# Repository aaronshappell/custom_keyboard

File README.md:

# custom_keyboard
Various files and resources for my handmade custom mechanical keyboard.

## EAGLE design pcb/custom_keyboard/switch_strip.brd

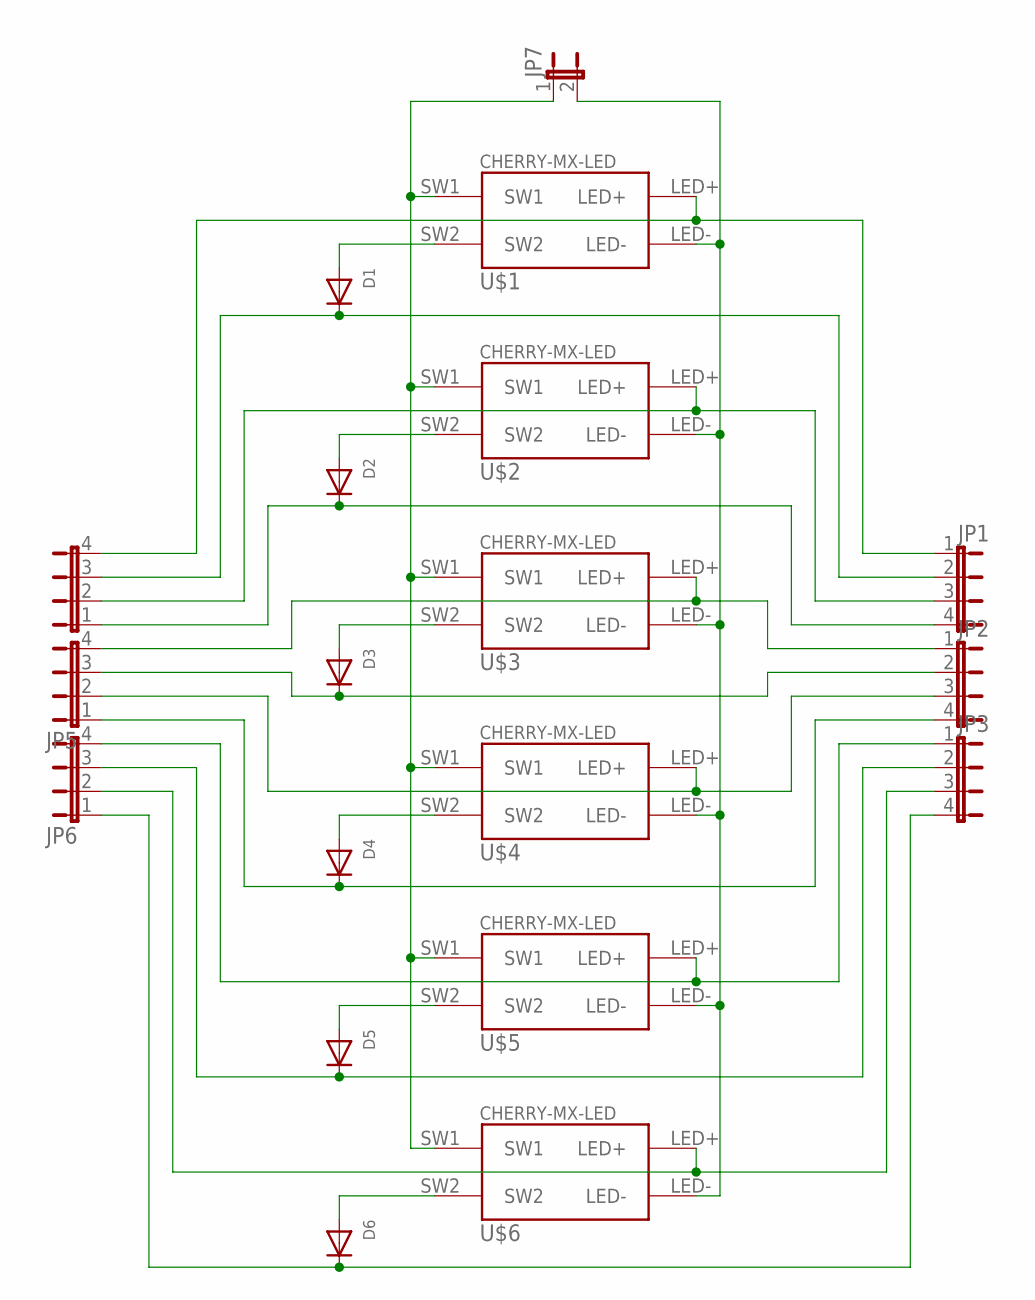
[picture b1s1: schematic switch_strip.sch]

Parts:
D1, D2, D3, D4, D5, D6: DIODEDO-1N4148; DO-1N4148
JP1, JP2, JP3, JP4, JP5, JP6: JP4E; JP4
JP7: JP1E; JP1
U$1, U$2, U$3, U$4, U$5, U$6: CHERRY-MX-LED

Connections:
unnamed: JP7.1, U$1.SW1, U$2.SW1, U$3.SW1, U$4.SW1, U$5.SW1, U$6.SW1
unnamed: D6.A, U$6.SW2
unnamed: D5.A, U$5.SW2
unnamed: D4.A, U$4.SW2
unnamed: D3.A, U$3.SW2
unnamed: D2.A, U$2.SW2
unnamed: D1.A, U$1.SW2
unnamed: JP7.2, U$1.LED-, U$2.LED-, U$3.LED-, U$4.LED-, U$5.LED-, U$6.LED-
unnamed: JP1.1, JP4.4, U$1.LED+
unnamed: D1.C, JP1.2, JP4.3
unnamed: JP1.3, JP4.2, U$2.LED+
unnamed: D2.C, JP1.4, JP4.1
unnamed: JP2.1, JP5.4, U$3.LED+
unnamed: D3.C, JP2.2, JP5.3
unnamed: JP2.3, JP5.2, U$4.LED+
unnamed: D4.C, JP2.4, JP5.1
unnamed: JP3.1, JP6.4, U$5.LED+
unnamed: D5.C, JP3.2, JP6.3
unnamed: JP3.3, JP6.2, U$6.LED+
unnamed: D6.C, JP3.4, JP6.1

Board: 2 copper layers, 19 parts (0 on the bottom side), 20 nets, no tracks yet.

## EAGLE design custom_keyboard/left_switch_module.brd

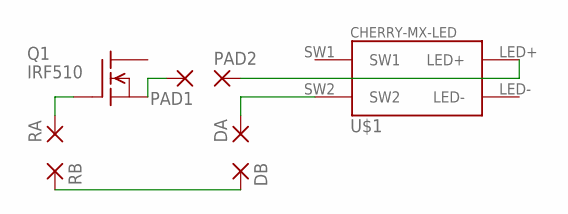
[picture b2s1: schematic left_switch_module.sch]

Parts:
DA: 2,15/1,0
DB: 2,15/1,0
PAD1, PAD2: 1,6/0,9
Q1: IRF510; TO220
RA: 2,15/1,0
RB: 2,15/1,0
U$1: CHERRY-MX-LED

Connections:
unnamed: Q1.1 (G), RA.1
unnamed: DB.1, RB.1
unnamed: DA.1, U$1.SW2
unnamed: PAD1.1, Q1.3 (S)
unnamed: PAD2.1, U$1.LED+

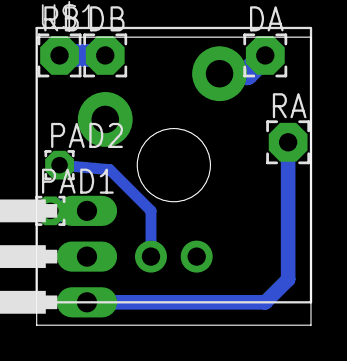
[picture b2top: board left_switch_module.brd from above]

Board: 2 copper layers, 15.2 x 16.0 mm, 8 parts (0 on the bottom side), 5 nets.

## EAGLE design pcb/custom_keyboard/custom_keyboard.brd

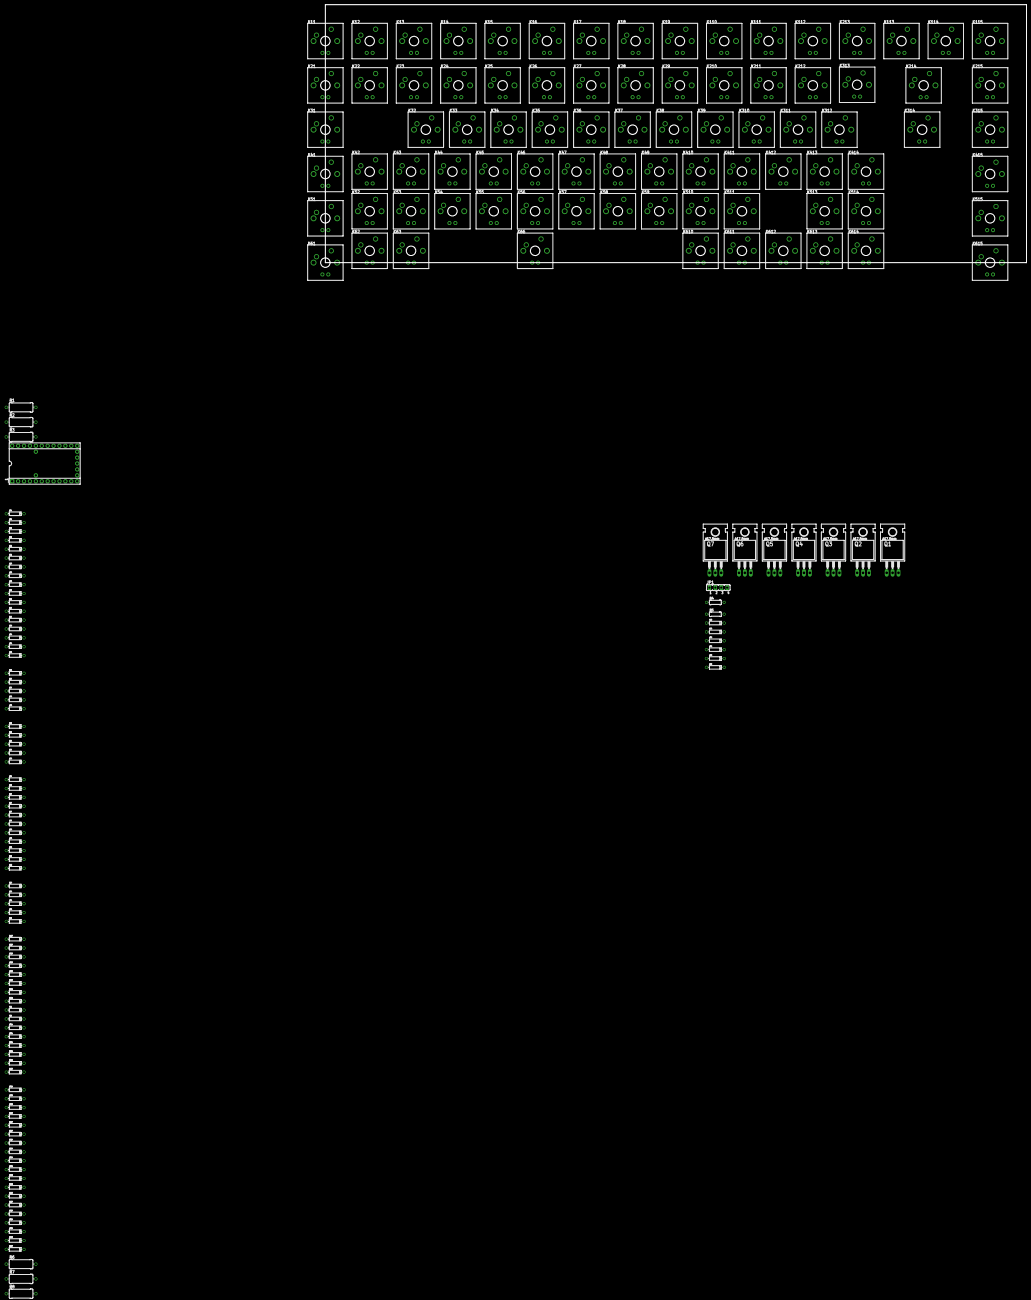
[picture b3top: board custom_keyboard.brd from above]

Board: 2 copper layers, 301.4 x 110.9 mm, 185 parts (0 on the bottom side), 120 nets, no tracks yet.

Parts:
311, 411: DO-1N4148
D11, D12, D13, D14, D15, D16, D17, D18, D19, D21, D22, D23, D24, D25, D26, D27, D28, D29, D31, D32, D33, D34, D35, D36, D37, D38, D39, D41, D42, D43, D44, D45, D46, D47, D48, D49, D51, D52, D53, D54, D55, D56, D57, D58, D59, D61, D62, D63, D66, D110, D111, D112, D113, D114, D115, D210, D211, D212, D213, D214, D215, D310, D312, D313, D314, D315, D410, D412, D413, D414, D415, D510, D511, D513, D514, D515, D610, D611, D612, D613, D614, D615: DO-1N4148
JP1: JP4
K11, K12, K13, K14, K15, K16, K17, K18, K19, K21, K22, K23, K24, K25, K26, K27, K28, K29, K31, K32, K33, K34, K35, K36, K37, K38, K39, K41, K42, K43, K44, K45, K46, K47, K48, K49, K51, K52, K53, K54, K55, K56, K57, K58, K59, K61, K62, K63, K66, K110, K111, K112, K113, K114, K115, K210, K211, K212, K213, K214, K215, K310, K311, K312, K313, K314, K315, K410, K411, K412, K413, K414, K415, K510, K511, K513, K514, K515, K610, K611, K612, K613, K614, K615: CHERRY-MX-LED
Q1, Q2, Q3, Q4, Q5, Q6, Q7: IRF510; TO220
R1, R2, R6, R7, R8: 6.8Ω; 0411/12
R3: 10Ω; 0411/12
R4, R5: 4.7kΩ; 0204/7
_1: TEENSY

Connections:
unnamed: D11.A, K11.SW2
unnamed: D12.A, K12.SW2
unnamed: D22.A, K22.SW2
unnamed: D21.A, K21.SW2
unnamed: D31.A, K31.SW2
unnamed: D41.A, K41.SW2
unnamed: D51.A, K51.SW2
unnamed: D61.A, K61.SW2
unnamed: D32.A, K32.SW2
unnamed: D42.A, K42.SW2
unnamed: D52.A, K52.SW2
unnamed: D62.A, K62.SW2
unnamed: D13.A, K13.SW2
unnamed: D23.A, K23.SW2
unnamed: D33.A, K33.SW2
unnamed: D43.A, K43.SW2
unnamed: D53.A, K53.SW2
unnamed: D63.A, K63.SW2
unnamed: D14.A, K14.SW2
unnamed: D24.A, K24.SW2
unnamed: D34.A, K34.SW2
unnamed: D44.A, K44.SW2
unnamed: D54.A, K54.SW2
unnamed: D11.C, D12.C, D13.C, D14.C, D15.C, D16.C, D17.C, D18.C, D19.C, D110.C, D111.C, D112.C, D113.C, D114.C, D115.C, Q1.1
unnamed: D15.A, K15.SW2
unnamed: D25.A, K25.SW2
unnamed: D35.A, K35.SW2
unnamed: D45.A, K45.SW2
unnamed: D55.A, K55.SW2
unnamed: D21.C, D22.C, D23.C, D24.C, D25.C, D26.C, D27.C, D28.C, D29.C, D210.C, D211.C, D212.C, D213.C, D214.C, D215.C, Q2.1
unnamed: D16.A, K16.SW2
unnamed: D26.A, K26.SW2
unnamed: D36.A, K36.SW2
unnamed: D46.A, K46.SW2
unnamed: D56.A, K56.SW2
unnamed: 311.C, D31.C, D32.C, D33.C, D34.C, D35.C, D36.C, D37.C, D38.C, D39.C, D310.C, D312.C, D313.C, D314.C, D315.C, Q3.1
unnamed: D17.A, K17.SW2
unnamed: D27.A, K27.SW2
unnamed: D37.A, K37.SW2
unnamed: D47.A, K47.SW2
unnamed: D57.A, K57.SW2
unnamed: D66.A, K66.SW2
unnamed: D18.A, K18.SW2
unnamed: D28.A, K28.SW2
unnamed: D38.A, K38.SW2
unnamed: D48.A, K48.SW2
unnamed: D58.A, K58.SW2
unnamed: 411.C, D41.C, D42.C, D43.C, D44.C, D45.C, D46.C, D47.C, D48.C, D49.C, D410.C, D412.C, D413.C, D414.C, D415.C, Q4.1
unnamed: D19.A, K19.SW2
unnamed: D29.A, K29.SW2
unnamed: D39.A, K39.SW2
unnamed: D49.A, K49.SW2
unnamed: D59.A, K59.SW2
unnamed: D51.C, D52.C, D53.C, D54.C, D55.C, D56.C, D57.C, D58.C, D59.C, D510.C, D511.C, D513.C, D514.C, D515.C, Q5.1
unnamed: D110.A, K110.SW2
unnamed: D210.A, K210.SW2
unnamed: D310.A, K310.SW2
unnamed: D410.A, K410.SW2
unnamed: D510.A, K510.SW2
unnamed: D610.A, K610.SW2
unnamed: D111.A, K111.SW2
unnamed: D211.A, K211.SW2
unnamed: 311.A, K311.SW2
unnamed: 411.A, K411.SW2
unnamed: D511.A, K511.SW2
unnamed: D611.A, K611.SW2
unnamed: D112.A, K112.SW2
unnamed: D212.A, K212.SW2
unnamed: D312.A, K312.SW2
unnamed: D412.A, K412.SW2
unnamed: D61.C, D62.C, D63.C, D66.C, D610.C, D611.C, D612.C, D613.C, D614.C, D615.C, Q6.1
unnamed: D612.A, K612.SW2
unnamed: D113.A, K113.SW2
unnamed: D213.A, K213.SW2
unnamed: D313.A, K313.SW2
unnamed: D413.A, K413.SW2
unnamed: D513.A, K513.SW2
unnamed: D613.A, K613.SW2
unnamed: D114.A, K114.SW2
unnamed: D214.A, K214.SW2
unnamed: D314.A, K314.SW2
unnamed: D414.A, K414.SW2
unnamed: D514.A, K514.SW2
unnamed: D614.A, K614.SW2
unnamed: D115.A, K115.SW2
unnamed: D215.A, K215.SW2
unnamed: D315.A, K315.SW2
unnamed: D415.A, K415.SW2
unnamed: D515.A, K515.SW2
unnamed: D615.A, K615.SW2
unnamed: K11.SW1, K21.SW1, K31.SW1, K41.SW1, K51.SW1, K61.SW1
unnamed: K12.SW1, K22.SW1, K32.SW1, K42.SW1, K52.SW1, K62.SW1
unnamed: K13.SW1, K23.SW1, K33.SW1, K43.SW1, K53.SW1, K63.SW1
unnamed: K14.SW1, K24.SW1, K34.SW1, K44.SW1, K54.SW1
unnamed: K115.SW1, K215.SW1, K315.SW1, K415.SW1, K515.SW1, K615.SW1
unnamed: K114.SW1, K214.SW1, K314.SW1, K414.SW1, K514.SW1, K614.SW1
unnamed: K113.SW1, K213.SW1, K313.SW1, K413.SW1, K513.SW1, K613.SW1
unnamed: K112.SW1, K212.SW1, K312.SW1, K412.SW1, K612.SW1
unnamed: K111.SW1, K211.SW1, K311.SW1, K411.SW1, K511.SW1, K611.SW1
unnamed: K110.SW1, K210.SW1, K310.SW1, K410.SW1, K510.SW1, K610.SW1
unnamed: K19.SW1, K29.SW1, K39.SW1, K49.SW1, K59.SW1
unnamed: K18.SW1, K28.SW1, K38.SW1, K48.SW1, K58.SW1
unnamed: K17.SW1, K27.SW1, K37.SW1, K47.SW1, K57.SW1
unnamed: K16.SW1, K26.SW1, K36.SW1, K46.SW1, K56.SW1, K66.SW1
unnamed: K15.SW1, K35.SW1, K45.SW1, K55.SW1
unnamed: Q1.3, R8.1
unnamed: Q2.3, R2.1
unnamed: Q3.3, R1.1
unnamed: Q4.3, R6.1
unnamed: Q5.3, R7.1
unnamed: Q1.2, Q2.2, Q3.2, Q4.2, Q5.2, Q6.2
unnamed: Q6.3, R3.1
unnamed: K11.LED-, K12.LED-, K13.LED-, K14.LED-, K15.LED-, K16.LED-, K17.LED-, K18.LED-, K19.LED-, K21.LED-, K22.LED-, K23.LED-, K24.LED-, K25.LED-, K26.LED-, K27.LED-, K28.LED-, K29.LED-, K31.LED-, K32.LED-, K33.LED-, K34.LED-, K35.LED-, K36.LED-, K37.LED-, K38.LED-, K39.LED-, K41.LED-, K43.LED-, K44.LED-, K45.LED-, K46.LED-, K47.LED-, K48.LED-, K49.LED-, K51.LED-, K52.LED-, K53.LED-, K54.LED-, K55.LED-, K56.LED-, K57.LED-, K58.LED-, K59.LED-, K61.LED-, K62.LED-, K63.LED-, K66.LED-, K110.LED-, K111.LED-, K112.LED-, K113.LED-, K114.LED-, K115.LED-, K210.LED-, K211.LED-, K212.LED-, K213.LED-, K214.LED-, K215.LED-, K310.LED-, K311.LED-, K312.LED-, K313.LED-, K314.LED-, K315.LED-, K410.LED-, K411.LED-, K412.LED-, K413.LED-, K414.LED-, K415.LED-, K510.LED-, K511.LED-, K513.LED-, K514.LED-, K515.LED-, K610.LED-, K611.LED-, K612.LED-, K613.LED-, K614.LED-, K615.LED-, Q7.2
unnamed: K11.LED+, K12.LED+, K13.LED+, K14.LED+, K15.LED+, K16.LED+, K17.LED+, K18.LED+, K19.LED+, K110.LED+, K111.LED+, K112.LED+, K113.LED+, K114.LED+, K115.LED+, R8.2
unnamed: K21.LED+, K22.LED+, K23.LED+, K24.LED+, K25.LED+, K26.LED+, K27.LED+, K28.LED+, K29.LED+, K210.LED+, K211.LED+, K212.LED+, K213.LED+, K214.LED+, K215.LED+, R2.2
unnamed: K31.LED+, K32.LED+, K33.LED+, K34.LED+, K35.LED+, K36.LED+, K37.LED+, K38.LED+, K39.LED+, K310.LED+, K311.LED+, K312.LED+, K313.LED+, K314.LED+, K315.LED+, R1.2
unnamed: K41.LED+, K42.LED+, K43.LED+, K44.LED+, K45.LED+, K46.LED+, K47.LED+, K48.LED+, K49.LED+, K410.LED+, K411.LED+, K412.LED+, K413.LED+, K414.LED+, K415.LED+, R6.2
unnamed: K51.LED+, K52.LED+, K53.LED+, K54.LED+, K55.LED+, K56.LED+, K57.LED+, K58.LED+, K59.LED+, K510.LED+, K511.LED+, K513.LED+, K514.LED+, K515.LED+, R7.2
unnamed: K61.LED+, K62.LED+, K63.LED+, K66.LED+, K610.LED+, K611.LED+, K612.LED+, K613.LED+, K614.LED+, K615.LED+, R3.2
unnamed: Q7.1, _1.B7

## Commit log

2018-07-14 Add initial files
2018-07-15 Add fusion files and teensy mount files
2018-07-15 Add firmware readme
2018-07-15 Work on keymap and layout
2018-07-15 Add keyboard layout json for reference
2018-07-15 Make file changes
2018-11-07 Revert to previous, delete parts folder
2018-11-13 Add wiring image and fix keyboard-layout.json
2018-11-13 Re gen project, fix matrix
2018-11-13 Enable backlighting and fix compile errors
2018-11-13 Fix pin defs
2018-11-13 Add backlight controls
2018-11-18 Add Eagle files
2018-11-18 Add datasheets
2018-11-18 Reorganize pcb eagle files
2018-11-18 Update switch pcb
2018-11-27 Add gitignore
2018-11-27 Remove backlighting for now
2019-04-18 Update gitignore
2019-04-18 Add initial kicad files
2019-04-18 Add switches to schematic
2019-07-04 Remove kicad files, add gaming layer, brightness control, debug/reset keys
2019-07-04 Actually remove kicad files
2019-07-04 Remove semicolons
2019-07-04 Add compiled hex file

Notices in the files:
parts and their libraries:
teensy: Licensed Under Creative Commons
